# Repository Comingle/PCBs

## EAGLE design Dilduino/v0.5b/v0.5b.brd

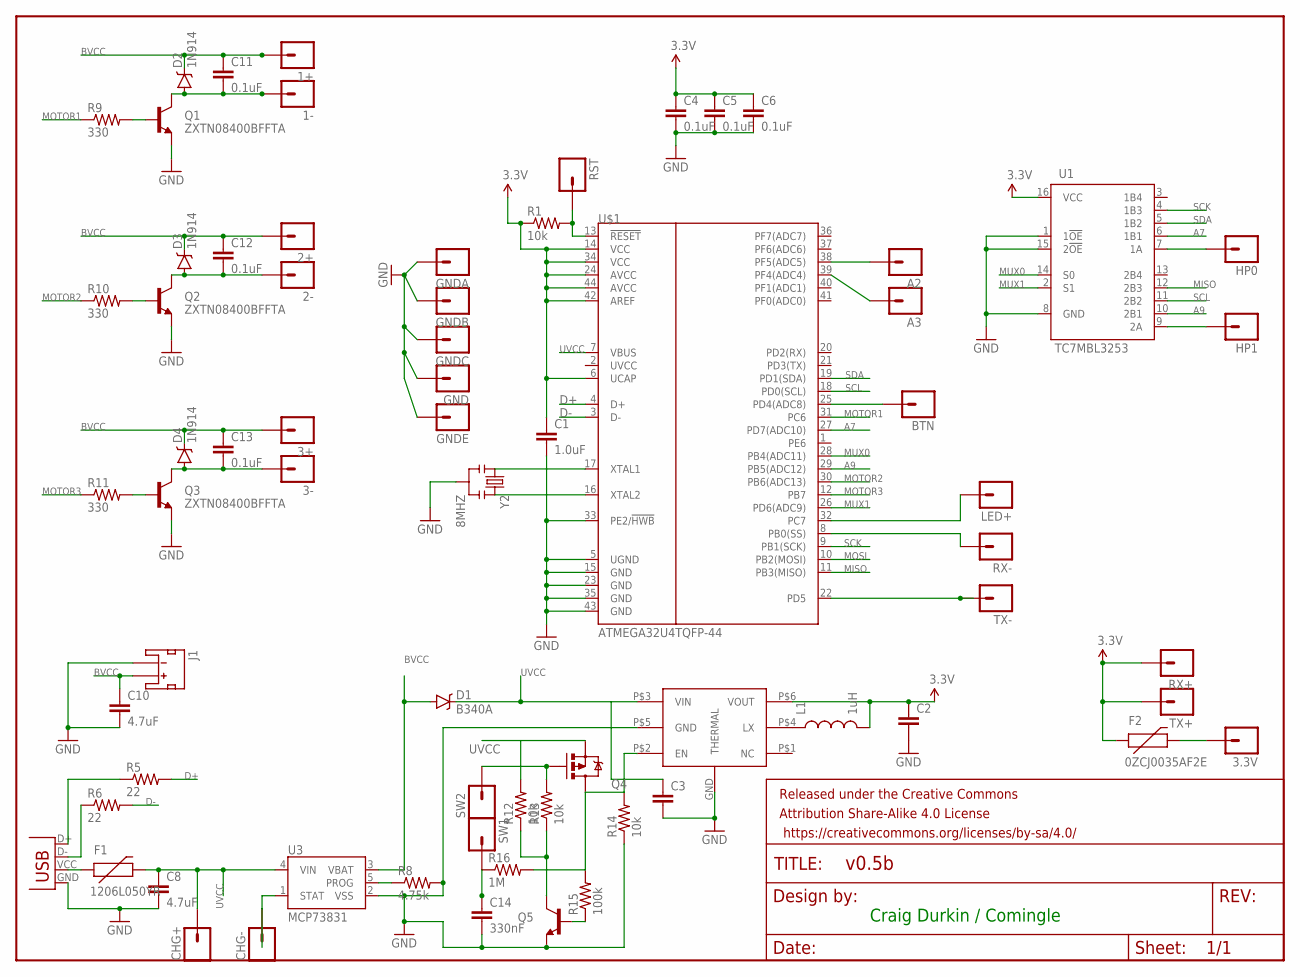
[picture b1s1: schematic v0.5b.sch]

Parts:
1+, 1-, 2+, 2-, 3+, 3-, 3.3V: M01PTH; 1X01
A2, A3: M01PTH; 1X01
BTN: M01PTH; 1X01
C1: 1.0uF; 0603-CAP
C2: CAP0805; 0805
C3: CAP0603-CAP; 0603-CAP
C4, C5, C6, C11, C12, C13: 0.1uF; 0603-CAP
C8, C10: 4.7uF; 1206
C14: 330nF; 0603-CAP
CHG+: M01PTH; 1X01
CHG-: M01PTH; 1X01
D1: B340A; SMA-DIODE
D2, D3, D4: 1N914; SOD-323
F1: 1206L050YR; PTC-1206
F2: 0ZCJ0035AF2E; PTC-1206
FRAME1: FRAME-LETTER; CREATIVE_COMMONS
GND: M01PTH; 1X01
GNDA: M01PTH; 1X01
GNDB: M01PTH; 1X01
GNDC: M01PTH; 1X01
GNDE: M01PTH; 1X01
HP0, HP1: M01PTH; 1X01
J1: JST_2MM_MALE; JST-2-SMD
JP4: USBMICROB-GCT-USB3075; USB-MICROB-GCT-USB3075
L1: 1uH; 1007
LED+: M01PTH; 1X01
Q1, Q2, Q3: ZXTN08400BFFTA; SOT23-3
Q4: NTS2101PT1G; SOT23-3
Q5: MMBT2222A; SOT23-3
R1, R12, R13, R14: 10k; 0603-RES
R5, R6: 22; 0603-RES
R8: 4.75k; 0603-RES
R9, R10, R11: 330; 0603-RES
R15: 100k; 0603-RES
R16: 1M; 0603-RES
RST: M01PTH; 1X01
RX+: M01PTH; 1X01
RX-: M01PTH; 1X01
SW1, SW2: M01PTH; 1X01
TX+: M01PTH; 1X01
TX-: M01PTH; 1X01
U1: TC7MBL3253; SSOP16-PRACTICE
U3: MCP73831; SOT23-5
U$1: ATMEGA32U4TQFP-44; TQFP44
U$3: SC189; MLPD-UT6
Y2: 8MHZ; RESONATOR-SMD

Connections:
3.3V: C2.1, L1.2, U$3.P$6 (VOUT)
A7: U1.6 (1B1), U$1.27 (PD7(ADC10))
A9: U1.10 (2B1), U$1.29 (PB5(ADC12))
BVCC: 1+.1, 2+.1, 3+.1, C10.1, C11.1, C12.1, C13.1, D1.A, D2.C, D3.C, D4.C, J1.2 (+), U3.3 (VBAT)
D+: R5.2, U$1.4 (D+)
D-: R6.2, U$1.3 (D-)
GND: C2.2, C3.2, U$3.GND (THERMAL)
GNDD: C1.2, C4.2, C5.2, C6.2, C8.2, C10.2, C14.2, GND.1, GNDA.1, GNDB.1, GNDC.1, GNDE.1, J1.1 (-), JP4.GND, Q1.2 (E), Q2.2 (E), Q3.2 (E), Q5.2 (E), R8.2, R14.1, U1.1 (1!OE), U1.8 (GND), U1.15 (2!OE), U3.2 (VSS), U$1.5 (UGND), U$1.15 (GND), U$1.23 (GND), U$1.33 (PE2/!HWB), U$1.35 (GND), U$1.43 (GND), U$3.P$5 (GND), Y2.2
MISO: U1.12 (2B3), U$1.11 (PB3(MISO))
MOSI: U$1.10 (PB2(MOSI))
MOTOR1: R9.1, U$1.31 (PC6)
MOTOR2: R10.1, U$1.30 (PB6(ADC13))
MOTOR3: R11.1, U$1.12 (PB7)
MUX0: U1.14 (S0), U$1.28 (PB4(ADC11))
MUX1: U1.2 (S1), U$1.26 (PD6(ADC9))
unnamed: U$1.17 (XTAL1), Y2.1
unnamed: R8.1, U3.5 (PROG)
unnamed: Q4.3 (D), R14.2, R15.2, R16.2, U$3.P$2 (EN)
unnamed: F1.1, JP4.VCC (VBUS)
unnamed: 3.3V.1, F2.2
unnamed: U$1.16 (XTAL2), Y2.3
unnamed: LED+.1, U$1.32 (PC7)
unnamed: RX-.1, U$1.8 (PB0(SS))
unnamed: TX-.1, U$1.22 (PD5)
unnamed: JP4.D+, R5.1
unnamed: JP4.D-, R6.1
unnamed: L1.1, U$3.P$4 (LX)
unnamed: HP1.1, U1.9 (2A)
unnamed: HP0.1, U1.7 (1A)
unnamed: A2.1, U$1.38 (PF5(ADC5))
unnamed: A3.1, U$1.39 (PF4(ADC4))
unnamed: BTN.1, U$1.25 (PD4(ADC8))
unnamed: CHG-.1, U3.1 (STAT)
unnamed: Q5.3 (C), R12.1, R13.1
unnamed: C14.1, R16.1, SW1.1
unnamed: Q4.1 (G), R13.2, SW2.1
unnamed: 1-.1, C11.2, D2.A, Q1.3 (C)
unnamed: 2-.1, C12.2, D3.A, Q2.3 (C)
unnamed: 3-.1, C13.2, D4.A, Q3.3 (C)
unnamed: Q1.1 (B), R9.2
unnamed: Q2.1 (B), R10.2
unnamed: Q3.1 (B), R11.2
unnamed: Q5.1 (B), R15.1
RST: R1.2, RST.1, U$1.13 (!RESET)
SCK: U1.4 (1B3), U$1.9 (PB1(SCK))
SCL: U1.11 (2B2), U$1.18 (PD0(SCL))
SDA: U1.5 (1B2), U$1.19 (PD1(SDA))
UVCC: C3.1, C8.1, CHG+.1, D1.C, F1.2, Q4.2 (S), R12.2, U3.4 (VIN), U$1.7 (VBUS), U$3.P$3 (VIN)
VCC: C1.1, C4.1, C5.1, C6.1, F2.1, R1.1, RX+.1, TX+.1, U1.16 (VCC), U$1.6 (UCAP), U$1.14 (VCC), U$1.24 (AVCC), U$1.34 (VCC), U$1.42 (AREF), U$1.44 (AVCC)

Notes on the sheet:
Craig Durkin / Comingle

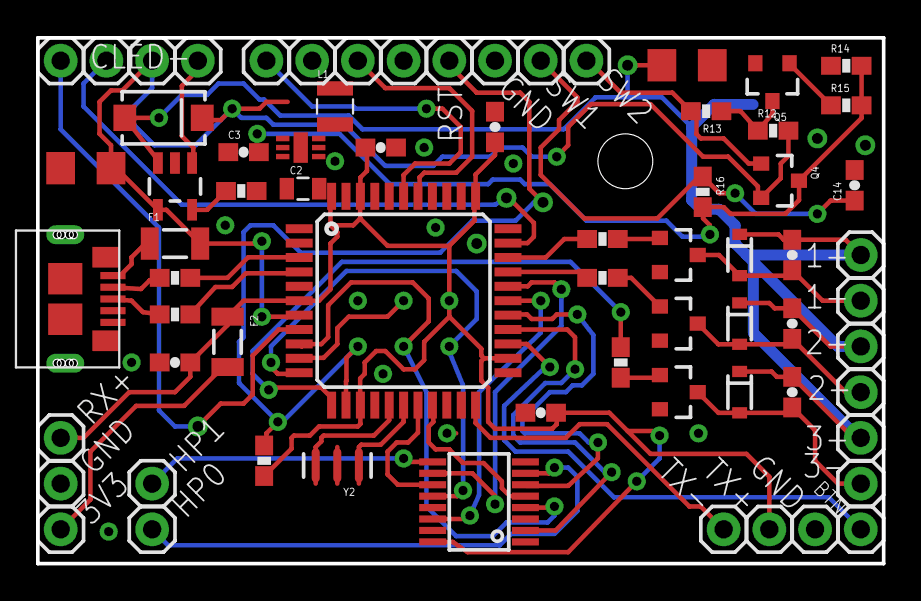
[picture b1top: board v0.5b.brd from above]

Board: 2 copper layers, 47.0 x 29.2 mm, 72 parts (1 on the bottom side), 48 nets.

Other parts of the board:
U$2: STAND-OFF-TIGHT

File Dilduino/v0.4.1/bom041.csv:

"Qty";"Value";"Device";"Package";"Parts";"Description";"PROD_ID";"VALUE";
"1";"";"JST_2MM_MALE";"JST-2-SMD";"J1";"Mates to single-cell LiPo batteries.";"CONN-08352";"";
"27";"";"M01PTH";"1X01";"1+, 1-, 2+, 2-, 3+, 3-, 3.3V, A2, A3, BTN, CHG+, CHG-, GND, GNDC, GNDE, GNDE1, GNDE2, LED+, OUT1, OUT2, RST, RX+, RX-, SW1, SW2, TX+, TX-";"Header 1";"";"";
"6";"0.1uF";"CAP0603-CAP";"0603-CAP";"C4, C5, C6, C11, C12, C13";"Capacitor";"";"";
"1";"1.0uF";"CAP0603-CAP";"0603-CAP";"C1";"Capacitor";"";"";
"1";"100k";"RESISTOR0603-RES";"0603-RES";"R15";"Resistor";"";"";
"5";"10k";"RESISTOR0603-RES";"0603-RES";"R1, R8, R12, R13, R14";"Resistor";"";"";
"1";"1206L016WR";"PTCSMD";"PTC-1206";"F2";"Resettable Fuse PTC";"RES-11150";"";
"1";"1206L050YR";"PTCSMD";"PTC-1206";"F1";"Resettable Fuse PTC";"RES-11150";"";
"1";"1M";"RESISTOR0603-RES";"0603-RES";"R16";"Resistor";"";"";
"2";"22";"RESISTOR0603-RES";"0603-RES";"R5, R6";"Resistor";"";"";
"2";"22pF";"CAP0603-CAP";"0603-CAP";"C2, C3";"Capacitor";"";"";
"3";"330";"RESISTOR0603-RES";"0603-RES";"R9, R10, R11";"Resistor";"";"";
"1";"330nF";"CAP0603-CAP";"0603-CAP";"C14";"Capacitor";"";"";
"1";"4.7uF";"CAP0603-CAP";"0603-CAP";"C7";"Capacitor";"";"";
"2";"4.7uF";"CAP1206";"1206";"C8, C10";"Capacitor";"";"";
"1";"470pF";"CAP0603-CAP";"0603-CAP";"C9";"Capacitor";"";"";
"1";"74CBTLV3253";"74CBTLV3253";"SSOP16-PRACTICE";"U1";"74CBT 2 x 4:1 multiplexer. 1OE and 2OE are output enable pins, and S0 and S1 determine which ouptut (xB4, xB3, ...) is connected to the xA";"";"";
"1";"8 MHz";"CRYSTAL5X3";"CRYSTAL-SMD-5X3";"Y1";"Various standard crystals. Proven footprints.";"XTAL-08218";"";
"1";"ATMEGA32U4TQFP-44";"ATMEGA32U4TQFP-44";"TQFP44";"U$1";"Atmel 44-pin 8-bit Microcontroller with 32KBytes of ISP Flash and USB Controller";"";"";
"1";"B340A";"DIODE-SCHOTTKY-B340A";"SMA-DIODE";"D1";"Schottky diodes in SFE's production catalog";"DIO-09886";"B340A";
"3";"BAT20JFILM";"BAT20JFILM";"SOD-323";"D2, D3, D4";"23V, 1A Schottky diode, SOD-323 package";"DIO-11623";"BAT20JFILM";
"1";"FRAME-LETTER";"FRAME-LETTER";"CREATIVE_COMMONS";"FRAME1";"Schematic Frame";"";"";
"1";"MCP73831";"MCP73831";"SOT23-5";"U3";"Miniature single cell, fully integrated Li-Ion, Li-polymer charge management controller";"IC-09995";"";
"1";"MIC5219 3.3V";"V_REG_MIC52193.3V";"SOT23-5";"U2";"V_REG MIC5219";"VREG-09872";"MIC5219 3.3V";
"1";"MMBT2222A";"TRANSISTOR_NPNMMBT2222A";"SOT23-3";"Q5";"Generic NPN BJT";"TRANS-08049";"MMBT2222A";
"1";"NTS2101PT1G";"MOSFET-PCHANNEL";"SOT23-3";"Q4";"Generic PMOSFET";"TRANS-08285";"";
"1";"USB";"USB";"USB-B-MICRO-SMD_V03";"JP4";"USB Connectors";"";"";
"3";"ZXTN08400BFFTA";"TRANSISTOR_NPNSOT23-3";"SOT23-3";"Q1, Q2, Q3";"Generic NPN BJT";"TRANS-08049";"";

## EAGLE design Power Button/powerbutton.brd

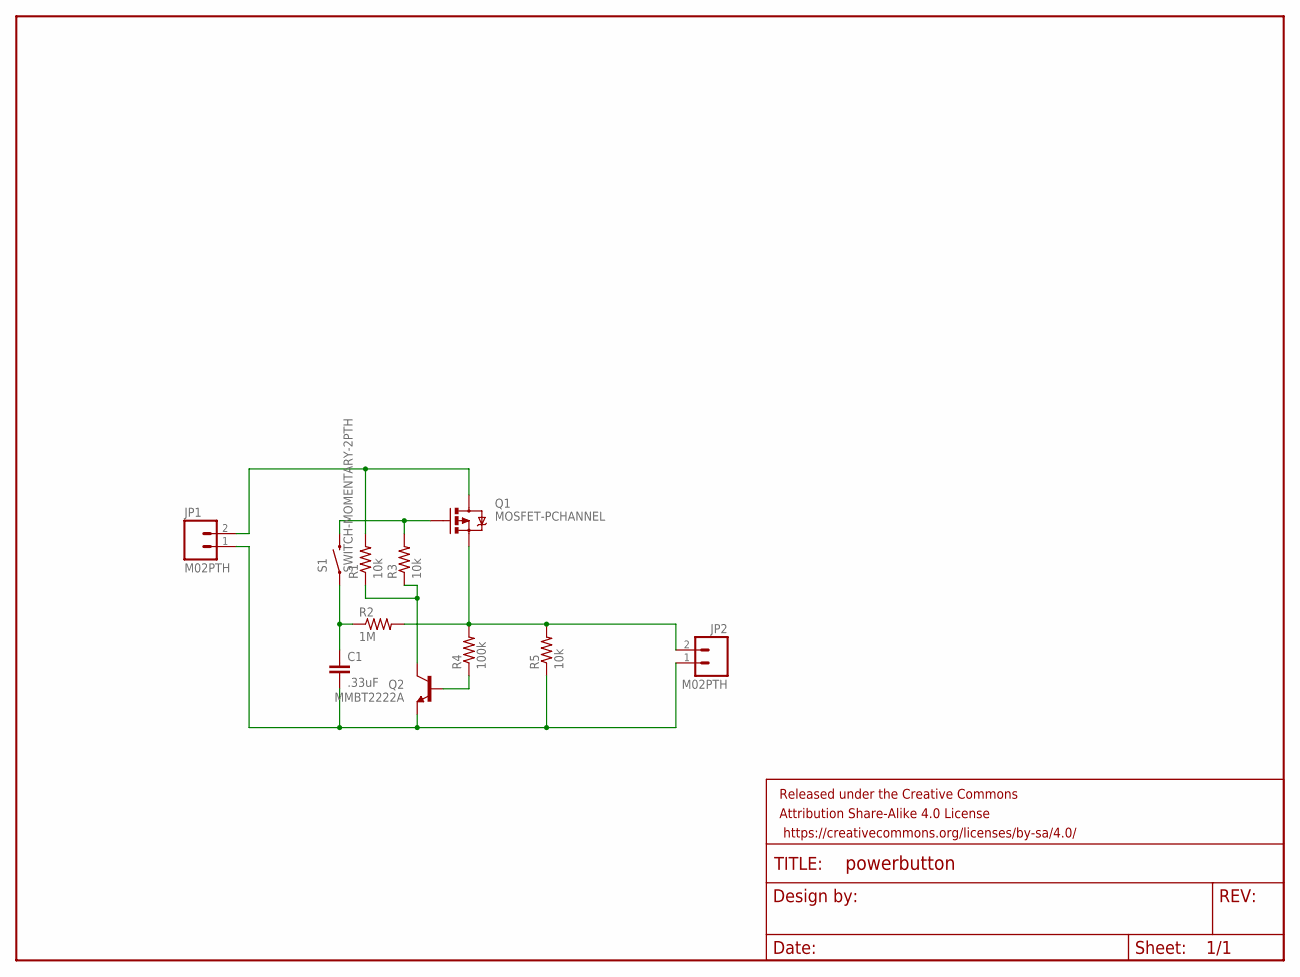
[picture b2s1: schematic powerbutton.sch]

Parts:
C1: .33uF; 0603-CAP
FRAME1: FRAME-LETTER; CREATIVE_COMMONS
JP1, JP2: M02PTH; 1X02
Q1: MOSFET-PCHANNEL; SOT23-3
Q2: MMBT2222A; SOT23-3
R1, R3, R5: 10k; 0603-RES
R2: 1M; 0603-RES
R4: 100k; 0603-RES
S1: SWITCH-MOMENTARY-2PTH; TACTILE-PTH

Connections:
unnamed: Q1.1 (G), R3.2, S1.3 (2)
unnamed: JP2.2, Q1.2 (S), R2.2, R4.2, R5.2
unnamed: Q2.1 (B), R4.1
unnamed: C1.1, R2.1, S1.1
unnamed: JP1.2, Q1.3 (D), R1.2
unnamed: Q2.3 (C), R1.1, R3.1
unnamed: C1.2, JP1.1, JP2.1, Q2.2 (E), R5.1

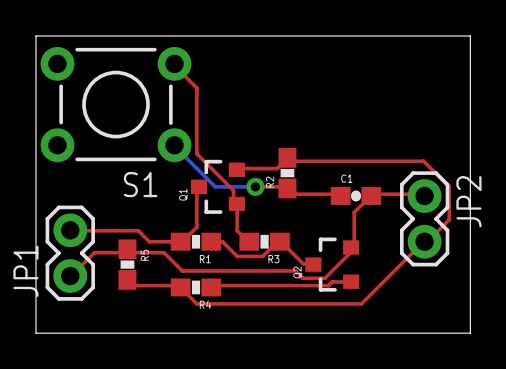
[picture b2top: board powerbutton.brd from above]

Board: 2 copper layers, 24.1 x 16.5 mm, 12 parts (0 on the bottom side), 7 nets.

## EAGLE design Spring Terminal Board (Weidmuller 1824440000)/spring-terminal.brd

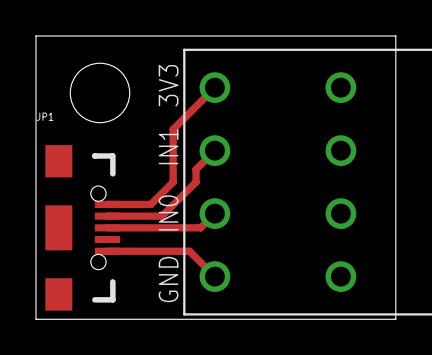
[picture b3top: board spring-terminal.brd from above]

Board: 2 copper layers, 20.0 x 15.7 mm, 3 parts (0 on the bottom side), 4 nets.

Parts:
JP1: USB; USB-B-MICRO-SMD_V03
JP2: 1X04_PUSH_BTN_TERM
U$1: STAND-OFF

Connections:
3V3: JP1.VBUS1, JP2.P$4
D+: JP1.D+1, JP2.P$2
D-: JP1.D-1, JP2.P$3
GND: JP1.GND1, JP2.P$1

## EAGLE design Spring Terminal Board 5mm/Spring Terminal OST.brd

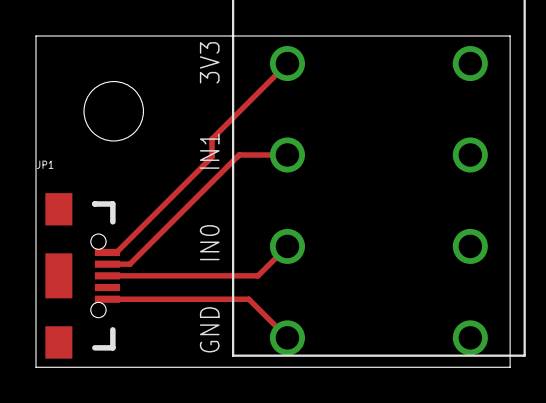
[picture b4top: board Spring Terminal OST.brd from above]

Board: 2 copper layers, 26.3 x 18.4 mm, 3 parts (0 on the bottom side), 4 nets.

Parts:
JP1: USB; USB-B-MICRO-SMD_V03
JP2: 1X04_SPRING_TERMINAL
U$1: STAND-OFF

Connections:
3V3: JP1.VBUS1, JP2.4
D+: JP1.D+1, JP2.2
D-: JP1.D-1, JP2.3
GND: JP1.GND1, JP2.1

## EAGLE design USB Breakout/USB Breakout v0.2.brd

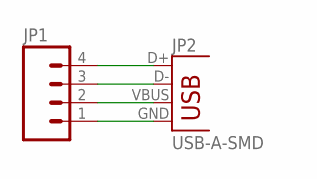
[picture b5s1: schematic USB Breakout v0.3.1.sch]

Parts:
JP1: M04LONGPADS; 1X04_LONGPADS
JP2: USB-A-SMD; USB-A-S-NOSILK-FEMALE

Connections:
3V3: JP1.2, JP2.VBUS
GND: JP1.1, JP2.GND
IN0: JP1.4, JP2.D+
IN1: JP1.3, JP2.D-

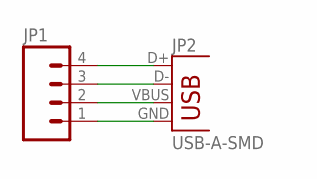
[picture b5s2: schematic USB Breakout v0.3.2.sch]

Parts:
JP1: M04LONGPADS; 1X04_LONGPADS
JP2: USB-A-SMD; USB-A-S-NOSILK-FEMALE

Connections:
3V3: JP1.2, JP2.VBUS
GND: JP1.1, JP2.GND
IN0: JP1.4, JP2.D+
IN1: JP1.3, JP2.D-

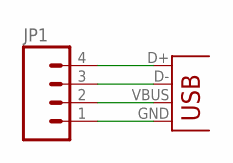
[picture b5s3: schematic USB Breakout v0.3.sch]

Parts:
JP1: M04LONGPADS; 1X04_LONGPADS
JP2: USB-A-SMD; USB-A-S-NOSILK-FEMALE

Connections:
3V3: JP1.2, JP2.VBUS
GND: JP1.1, JP2.GND
IN0: JP1.4, JP2.D+
IN1: JP1.3, JP2.D-

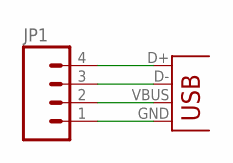
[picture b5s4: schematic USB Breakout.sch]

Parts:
JP1: M04PTH; 1X04
JP2: USB-A-SMD; USB-A-S-NOSILK-FEMALE

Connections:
3V3: JP1.2, JP2.VBUS
GND: JP1.1, JP2.GND
IN0: JP1.4, JP2.D+
IN1: JP1.3, JP2.D-

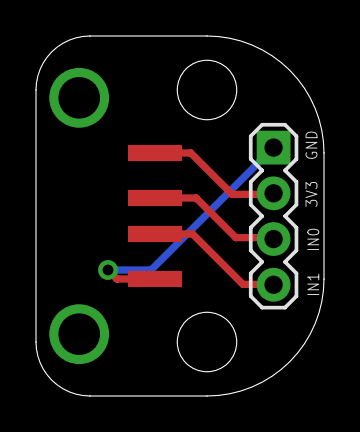
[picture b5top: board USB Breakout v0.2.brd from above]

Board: 2 copper layers, 16.0 x 20.0 mm, 4 parts (0 on the bottom side), 4 nets.

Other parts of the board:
U$1, U$2: STAND-OFF

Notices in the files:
parts and their libraries:
SparkFun-Capacitors: Licensing: Creative Commons ShareAlike 4.0 International - https://creativecommons.org/licenses/by-sa/4.0
SparkFun-Aesthetics: Released under the Creative Commons Attribution Share-Alike 4.0 License
SparkFun-Aesthetics: https://creativecommons.org/licenses/by-sa/4.0
